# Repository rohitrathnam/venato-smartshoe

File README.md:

# Venato Smart Shoe
HL2032 team project to create a smart shoe that measures pressure distribution and gait parameters of the feet. 

## Lean Canvas

### Problem
1. Conditioning coach: As a conditioning coach, I want to have deep analysis of foot pressure during exercises such as squats or deadlift.  Plus, I want to perform kinetic tests that requires Force plates and labs, anytime. maybe after a workout. Besides, jumping parameters, such as impact time, landing forces etc are really important in order to prevent injuries for me.
1. As a fitness user, I want track my fitness through step counts and visualise on my devices
1. As a senior care provider, I want the device to record foot pressure distributions to track posture and joint health
2. As a physiotherapist, I want to visualise the different gait parameters to assess posture and monitor corrections
3. As a user I want the device to be wireless for ease of use

### Customer-segment
1. Fitness tracking
1. Gait / posture correction
1. Senior care
2. Rehabilitation

### Unique-Value-Proposition
**Single**, _clear_, `compelling` message that states why you are different and worth buying
- Compatible with any shoe
- Foot pressure distribution, stride duration, step duration, swing and stance duration, gait cadence, gait frequency, double support duration, velocity
- Supports outdoor tracking
- Low cost alternative
- Product ecosystem - mobile / desktop / browser to visualise data

### Solution
- Create a bluetooth enabled sole with contact force, gyros and IMU which can be slipped any shoe

### Channels
- Retailers (online/specialized stores/mainstream stores)
- Physiotherapist
- Social media
- Point of sale

### Cost-Structure
- Customer aquisition costs
- Distribution costs
- Hosting
- People
- Parts

### Revenue-Stream
- Unit sales 
- Subscription for personalised analytics
- Strategic partnerships with training / rehab centres

### Key-Metrics
- Sensitivity, accuracy, specificity, repeatability, reliability of measurements
- Response time 
- Battery life 
- Position of pressure points
- Another key activity to measure

### Unfair-advantage
- New intellectual property
- Currently no competition

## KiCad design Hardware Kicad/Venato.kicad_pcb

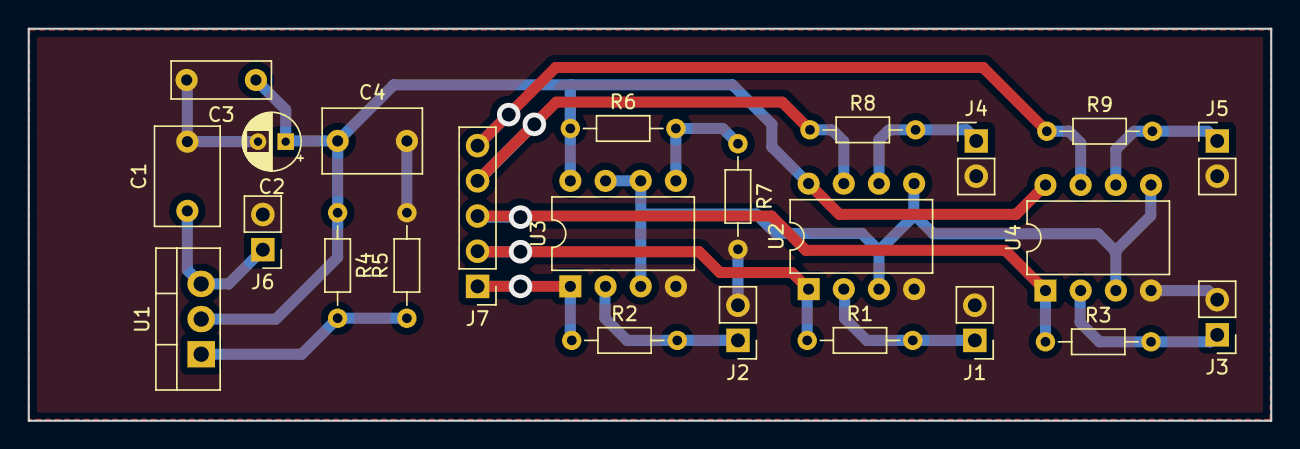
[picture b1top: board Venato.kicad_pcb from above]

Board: 2 copper layers, 89.7 x 28.3 mm, 24 parts (0 on the bottom side), 16 nets.

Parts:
C1, C4: 1u; C_Rect_L7.0mm_W4.5mm_P5.00mm
C2: 10u; CP_Radial_D4.0mm_P2.00mm
C3: 0.1u; C_Rect_L7.0mm_W2.5mm_P5.00mm
J1, J2, J3, J4, J5, J6: Conn_01x02_Male; PinHeader_1x02_P2.54mm_Vertical
J7: Conn_01x05_Male; PinHeader_1x05_P2.54mm_Vertical
R1, R2, R3, R8, R9: 1.5k; R_Axial_DIN0204_L3.6mm_D1.6mm_P7.62mm_Horizontal
R4: 270; R_Axial_DIN0204_L3.6mm_D1.6mm_P7.62mm_Horizontal
R5: 180; R_Axial_DIN0204_L3.6mm_D1.6mm_P7.62mm_Horizontal
R6: 42k; R_Axial_DIN0204_L3.6mm_D1.6mm_P7.62mm_Horizontal
R7: 9k; R_Axial_DIN0204_L3.6mm_D1.6mm_P7.62mm_Horizontal
U1: LM317_TO-220; TO-220-3_Vertical
U2, U3, U4: MCP6002-xP; DIP-8_W7.62mm

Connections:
+3.3VA: C2.1, C3.1, C4.1, R4.1, R6.1, U1.2, U2.8, U3.8, U4.8
+5V: C1.1, J6.1, U1.3
GND: C1.2, C2.2, C3.2, C4.2, J1.2, J2.2, J3.2, J4.2, J5.2, J6.2, R5.2, R7.2, U2.4, U3.4, U4.4
unnamed: J1.1, R1.2, U2.2
unnamed: J2.1, R2.2, U3.2
unnamed: J3.1, R3.2, U4.2
unnamed: J4.1, R8.2, U2.6
unnamed: J5.1, R9.2, U4.6
unnamed: R4.2, R5.1, U1.1
unnamed: R6.2, R7.1, U3.5
SENSE1: J7.2, R1.1, U2.1
SENSE2: J7.1, R2.1, U3.1
SENSE3: J7.5, R9.1, U4.7
SENSE4: J7.3, R3.1, U4.1
SENSE5: J7.4, R8.1, U2.7
VGND: U2.3, U2.5, U3.3, U3.6, U3.7, U4.3, U4.5

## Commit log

2021-09-15 added lean canvas
2021-09-15 added lean canvas support
2021-09-15 fixed readme
2021-09-15 fix readme
2021-09-15 testing branch
2021-09-16 added conditioning coach
2021-09-16 3 graph windows works
2021-09-23 just testing
2021-09-27 Opamp schematic
2021-09-30 Added PCB
    DRC ok, need to generate gerbers
2021-10-04 testin imu
2021-10-04 imu test d1
2021-10-04 imu ino
2021-10-04 temporary
2021-10-05 graphing issue
2021-10-07 test
2021-10-12 gerbers
2021-11-05 Add files via upload
    The Arduino code for Bluetooth communication.
2021-11-17 v2 pcb init
2021-11-24 ble sends bytes
2021-11-24 1mm traces and fix resistor
2022-01-02 updated arduino code
2022-01-04 bluetooth transfer in big chunks
2022-01-04 added matlab for float ble chunks
2022-01-07 v2 pcb done
2022-01-08 updated, smartshoe.ino broke
2022-01-09 Matlab code for plaotting FSR
2022-01-09 updated repo
2022-01-09 removing files due to conflict
2022-01-09 reorganising
2022-01-09 Logs and Media
2022-01-09 Calibration code
    Matlab code for IMU calibration
2022-01-10 updated codes
2022-01-11 Presentation
2022-01-11 Added some vid files
2022-01-11 added final report
2022-01-18 redo names
